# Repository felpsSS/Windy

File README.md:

# 🌬️ Windy: Build Your Air Quality Device!

Welcome to the **Windy** repository! This folder contains everything you need to build our air quality device. Whether you are a hobbyist, student, or professional, you will find useful resources here. 

## 📦 Table of Contents

- [Introduction](#introduction)
- [Features](#features)
- [Getting Started](#getting-started)
- [Hardware Components](#hardware-components)
- [Software Setup](#software-setup)
- [3D Printing](#3d-printing)
- [Mobile Application](#mobile-application)
- [PCB Design](#pcb-design)
- [Contributing](#contributing)
- [License](#license)
- [Contact](#contact)
- [Releases](#releases)

## 📜 Introduction

Air quality is vital for our health and well-being. With the **Windy** device, you can monitor air quality in real-time. This project combines various technologies, including sensors, microcontrollers, and mobile applications. 

## 🌟 Features

- Real-time air quality monitoring
- User-friendly mobile application for Android and iOS
- Open-source design for easy customization
- 3D-printed housing for a sleek look
- Easy-to-follow instructions

## 🚀 Getting Started

To get started with the **Windy** project, follow these steps:

1. **Clone the Repository**
   ```bash
   git clone https://github.com/felpsSS/Windy.git
   ```

2. **Navigate to the Directory**
   ```bash
   cd Windy
   ```

3. **Check the Documentation**
   Refer to the `docs` folder for detailed instructions.

## 🛠️ Hardware Components

To build the **Windy** device, you will need the following components:

- **ESP32 Microcontroller**: This will be the brain of your device.
- **Air Quality Sensor**: Choose a sensor that meets your needs (e.g., MQ-135).
- **Power Supply**: Ensure you have a reliable power source.
- **3D Printed Case**: You can find the design files in the `3D-Print` folder.

### Recommended Components

| Component          | Description                      |
|--------------------|----------------------------------|
| ESP32              | Dual-core microcontroller        |
| MQ-135 Sensor      | Measures air quality             |
| Battery Pack       | For portable use                 |
| Jumper Wires       | For connections                  |

## 💻 Software Setup

The software setup involves several steps:

1. **Install the Arduino IDE**: Download from the [official website](https://www.arduino.cc/en/software).
2. **Install ESP32 Board Support**: Follow the instructions in the Arduino IDE to add ESP32 support.
3. **Upload the Code**: Open the `Windy.ino` file and upload it to your ESP32.

### Libraries Required

Make sure to install the following libraries in the Arduino IDE:

- `DHT sensor library`
- `WiFi library`
- `HTTPClient library`

## 🖨️ 3D Printing

To create the housing for your **Windy** device, you will need to 3D print the case. The STL files are located in the `3D-Print` folder. 

### Printing Guidelines

- **Material**: Use PLA or ABS for durability.
- **Layer Height**: 0.2 mm for a good balance of quality and speed.
- **Infill**: 20% should be sufficient.

## 📱 Mobile Application

The **Windy** mobile application is available for both Android and iOS. It allows you to monitor air quality data from your device.

### Features of the App

- Real-time data display
- Historical data tracking
- Alerts for poor air quality
- User-friendly interface

### Installation

You can download the mobile app from the respective app stores. 

## 🛠️ PCB Design

The PCB design files are included in the repository. You can modify them as needed. 

### Design Software

We recommend using KiCAD or Eagle for PCB design. 

## 🤝 Contributing

We welcome contributions! If you want to improve the **Windy** project, please follow these steps:

1. Fork the repository.
2. Create a new branch.
3. Make your changes.
4. Submit a pull request.

## 📜 License

This project is licensed under the MIT License. See the `LICENSE` file for details.

## 📞 Contact

For questions or feedback, feel free to reach out:

- **Email**: your-email@example.com
- **GitHub**: [felpsSS](https://github.com/felpsSS)

## 🚀 Releases

For the latest updates and releases, visit our [Releases](https://github.com/felpsSS/Windy/releases) section. You can download the necessary files and execute them as needed.

---

Thank you for checking out the **Windy** project! We hope you enjoy building your air quality device. For any further questions, please refer to the documentation or contact us directly.

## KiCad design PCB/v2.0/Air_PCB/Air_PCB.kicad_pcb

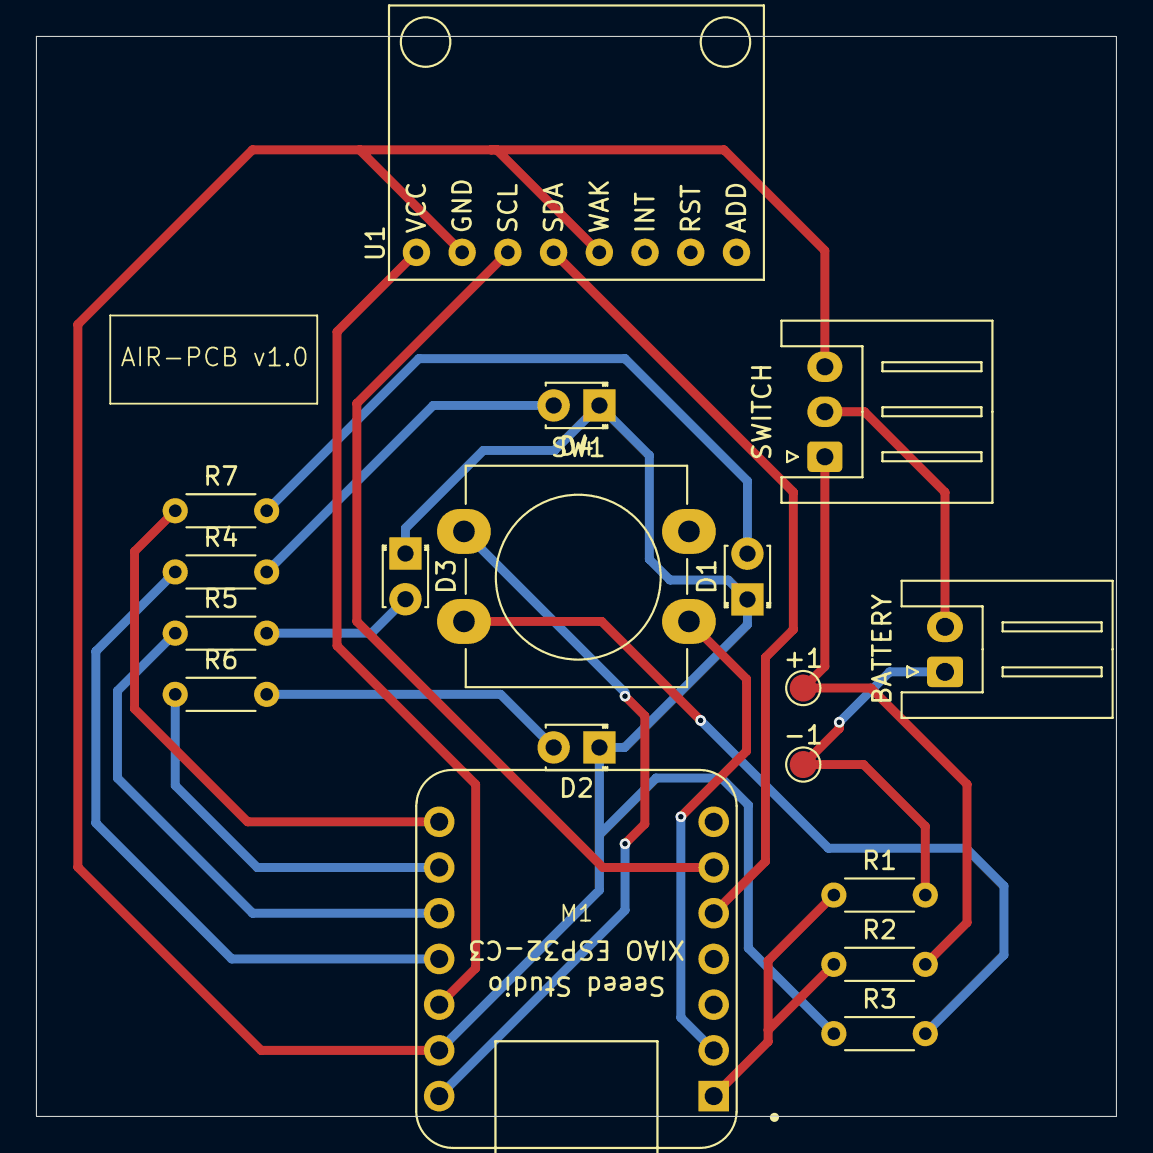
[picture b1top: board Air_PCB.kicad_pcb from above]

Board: 2 copper layers, 60.0 x 60.0 mm, 18 parts (0 on the bottom side), 19 nets.

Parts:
+1: Conn_01x01_Pin; TestPoint_Pad_D1.5mm
-1: Conn_01x01_Pin; TestPoint_Pad_D1.5mm
BATTERY: Conn_01x02_Socket; JST_XH_S2B-XH-A_1x02_P2.50mm_Horizontal
D1, D2, D3, D4: LED; LED_D1.8mm_W3.3mm_H2.4mm
M1: XIAO Connector/DNP; XIAO-Generic-Thruhole-14P-2.54-21X17.8MM
R1, R2, R3, R4, R5, R6, R7: R; R_Axial_DIN0204_L3.6mm_D1.6mm_P5.08mm_Horizontal
SW1: SW_Push_Open_Dual; SW_PUSH-12mm_Wuerth-430476085716
SWITCH: Conn_01x03_Socket; JST_XH_S3B-XH-A_1x03_P2.50mm_Horizontal
U1: module_CJMCUCCS811; module_adxl345

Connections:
unnamed: +1.1, R2.2, SWITCH.1
unnamed: -1.1, BATTERY.1, R1.2
unnamed: D1.2 (A), R7.2
unnamed: D1.1 (K), D2.1 (K), D3.1 (K), D4.1 (K), M1.13 (GND), R3.1, SWITCH.3, U1.2 (GND), U1.5 (WAK)
unnamed: D2.2 (A), R6.2
unnamed: D3.2 (A), R5.2
unnamed: D4.2 (A), R4.2
unnamed: BATTERY.2, SWITCH.2
unnamed: M1.12 (3V3), U1.1 (VCC)
unnamed: M1.1 (D0/A0), R1.1, R2.1
unnamed: M1.2 (D1/A1), SW1.2
unnamed: M1.5 (D4/SDA), U1.4 (SDA)
unnamed: M1.6 (D5/SCL), U1.3 (SCL)
unnamed: M1.8 (D7/RX/SS), R7.1
unnamed: M1.9 (D8/SCK), R6.1
unnamed: M1.10 (D9/MISO), R5.1
unnamed: M1.11 (D10/MOSI), R4.1
unnamed: M1.14 (VUSB), SW1.3
unnamed: R3.2, SW1.4
